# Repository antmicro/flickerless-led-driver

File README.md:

# OSRAM LZ1 LuxiGen LED driver

Copyright (c) 2023 [Antmicro](https://www.antmicro.com) 

## Overview 

This project contains open hardware design files for a PCB supporting a pair of LEDs in LZ1 LuxiGen package from OSRAM.
The PCB includes a flickerless LED driver allowing to adjust LED brightness with a potentiometer.
This design can be easily adopted to other LEDs and eventually can become a custom LED driver providing precise lighting for machine vision applications.

The design files were prepared in KiCad 6.x.

# Key features 

* LED current driver implemented with MPS/MP2483DQ-LF-P
* Designed for a pair of LZ1-00R802-0000
* Can be daisy-chained with multiple LEDs driven with a single driver

## Project structure

The main directory contains KiCad PCB project files, a LICENSE, and a README.
The remaining files are stored in the following directories:

* `lib` - contains the component libraries
* `img` - contains graphics for this README

## Usage

The project contains one PCB that can be configured as a primary or a secondary. 
It is designed to be powered with 12V DC using a barrel jack. It was tested on the highest britgness settings in a chain of 3 boards with a digital microscope as load on USB-C, the current in a circuit was around 1A. 

**Primary board** 

It's the board that contains the LED driver, all the connectors and a potentiometer. 

There are 3 connectors on the primary board: 
* USB-C - outputs 5V without data transfer, only to power some additional device, i.e. a microscope or a camera
* A barrel jack to power the whole circuit wih 12V
* A 2-pin JST connector - to daisy chain boards with diodes in serial connection 

A rotary potentiometer is the element that provides control of diode brightness using the LED driver. 

**Secondary board** 

It only contains the LZ1 diodes, 2-pin connectors and resistors marked as secondary DP (R10 and R7). It is powered and controlled by the primary board through JST connectors. 

> **Single board circuit** 
> To configure the primary board as a standalone, mount the R7 Debug jumper in addition to R11. 

> **Multiboard circuit** 
> To daisy chain the boards R7 CAN NOT be populated on primary board and must be populated on secondary boards. C_out of one board must be connected to A_in of another one. The design was made for 3 boards in a chain. To connect more boards higher voltage and possibly changing some passives will be required. 

## Licensing

This project is published under the [Apache-2.0](LICENSE) license.

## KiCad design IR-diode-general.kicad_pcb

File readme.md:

## Power IR-LEDs driver 
The project consists of 3 similar PCBs. Each of them has 2 LZ1-00R802 diodes. One also has a buck converter that serves as a LED driver for all 3 PCBs. They are daisy-chained into one circuit in order to attach them to a digital microscope, using which we can see through sillicon and observe chip structures.

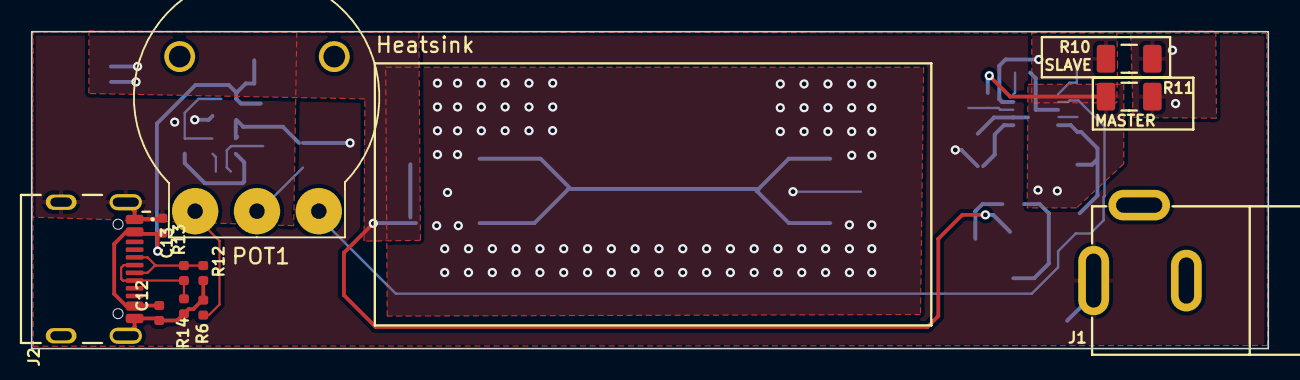
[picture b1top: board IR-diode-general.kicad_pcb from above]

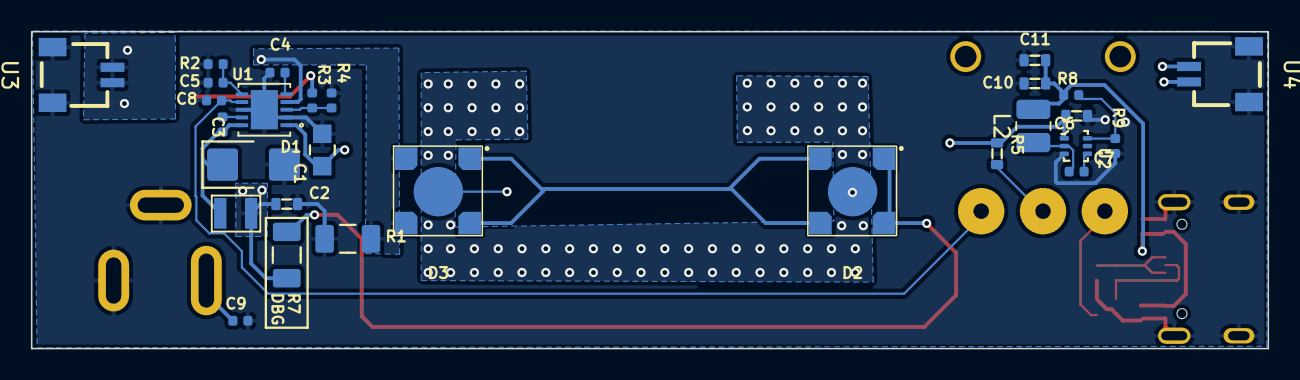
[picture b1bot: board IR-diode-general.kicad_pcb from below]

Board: 2 copper layers, 80.0 x 20.5 mm, 39 parts (28 on the bottom side), 22 nets.

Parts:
C1: C_10u_0805; 0805-cap
C2: C_2u2_0603; 0603-cap
C3, C7, C8, C9, C12, C13: C_100n_0402; C_0402_1005Metric
C4, C5: C_1n0_0402; 0402-cap
C6: C_10u_25V_0603; C_0603_1608Metric
C10, C11: C_22u_0603; C_0603_1608Metric
D1: B360A-M3; DO-214AC
D2, D3: LZ1-00R802-0000; LZ1-00R802_4EP_4.4x4.4
J1: BarrelJack_3167288; BarrelJack_3167288_Horizontal
J2: USB4105-GF-A; GCT_USB4105-GF-A
L1: SRP2512A-4R7M; SRP2512A-1R0M
L2: TFM252012ALMA3R3MTAA; L_1008_2520Metric
POT1: R0141-2-20k; Potentiometer_SRPassives_R0141-2_Horizontal
R1: R_0R2_1206; 1206-res
R2: R_39k_0402; 0402-res
R3: R_18k_0402; 0402-res
R4: R_2k_0402; R_0402_1005Metric
R5: R_300k_0603; 0603-res
R6: R_20k_0402; R_0402_1005Metric
R7, R10, R11: R_0R_1206; R_1206_3216Metric
R8: R_6k8_0402; 0402-res
R9: R_1k3_0402; R_0402_1005Metric
R12, R14: R_10k_0402; R_0402_1005Metric
R13: R_100R_0402; R_0402_1005Metric
U1: MP2483DQ-LF-P
U2: AP62301Z6-7; SOT-563
U3, U4: SM02B-SRSS-TB-LF-SN; JST_SM02B-SRSS-TB(LF)(SN)

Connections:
+12V: C1.2, C6.2, C9.2, J1.1, R5.2, U1.1 (VDD), U2.1 (VIN)
/LED DRIVER & USB-C Power output/VBUS: C10.2, C11.2, C12.2, C13.2, J2.A4 (VBUS), J2.A9 (VBUS), J2.B4 (VBUS), J2.B9 (VBUS), L2.2, R8.2
A_in: D2.2 (A), D2.3 (A), R7.1, U4.1, U4.2
C_out: R10.1, R11.1, U3.1, U3.2
FB: D3.1 (C), D3.4 (C), R1.2, R10.2, U1.4 (FB)
GND: C1.1, C2.1, C4.1, C5.1, C6.1, C8.1, C9.1, C10.1, C11.1, C12.1, C13.1, D1.A, J1.2, J1.3, J2.A1 (GND), J2.A12 (GND), J2.B1 (GND), J2.B12 (GND), J2.S1 (SHIELD), R1.1, R2.1, R4.2, R6.1, R9.1, R12.1, R14.1, U1.2 (VSS), U1.8 (INGND), U1.EPAD, U2.3 (GND), U3.3 (SHIELD), U3.4 (SHIELD), U4.3 (SHIELD), U4.4 (SHIELD)
unnamed: C3.1, D1.K, L1.1, U1.10 (SW)
unnamed: C3.2, U1.9 (BST)
unnamed: C4.2, U1.5 (COMP)
unnamed: C5.2, R2.2, U1.6 (RSET)
unnamed: C7.1, U2.4 (BST)
unnamed: C7.2, L2.1, U2.2 (SW)
unnamed: C8.2, POT1.3, U1.7 (EN/DIM)
unnamed: D2.1 (C), D2.4 (C), D3.2 (A), D3.3 (A)
unnamed: J2.A6 (D+), J2.B6 (D+), R13.1, R14.2
unnamed: J2.A7 (D-), J2.B7 (D-), R12.2, R13.2
unnamed: POT1.1, R6.2
unnamed: POT1.2, R5.1
unnamed: R3.2, R4.1, U1.3 (OVP)
unnamed: R8.1, R9.2, U2.6 (FB)
SW: C2.2, L1.2, R3.1, R7.2, R11.2
Thermal: D2.5 (T), D3.5 (T)

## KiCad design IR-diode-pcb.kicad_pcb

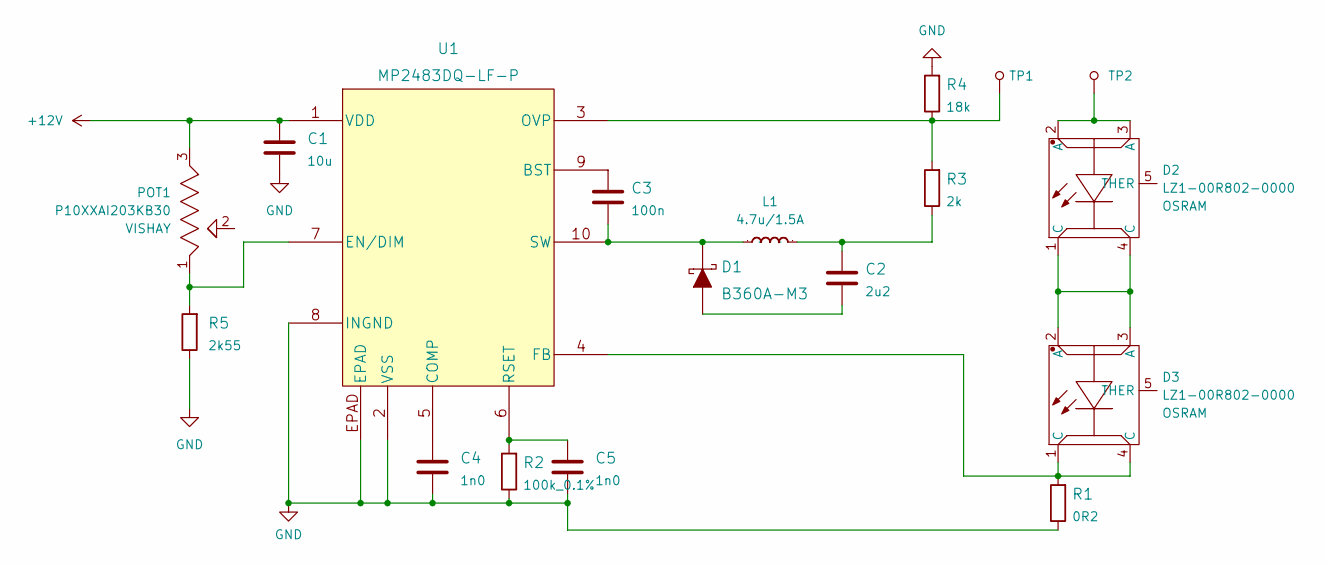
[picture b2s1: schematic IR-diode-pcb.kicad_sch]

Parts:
C1: C_10u_0402; 0402-cap; MPN CC0402MRX5R5BB106
C2: C_2u2_0402; 0402-cap; MPN C1005X5R1A225K050BC
C3: C_100n_0402; 0402-cap; MPN GRM155R61H104KE14D
C4, C5: C_1n0_0402; 0402-cap; MPN 885012005018
D1: B360A-M3; DO-214AC; MPN B360A-M3/61T
D2, D3: LZ1-00R802-0000; LZ1-00R802_4EP_4.4x4.4; MPN LZ1-00R802-0000
L1: SRP2512A-4R7M; SRP2512A-1R0M; MPN SRP2512A-1R0M
POT1: P10XXAI203KB30; MPN P10XXAI203KB30
R1: R_0R2_1206; 1206-res; MPN ERJ-8BSFR20V
R2: R_100k_0.1%_0402; 0402-res; MPN RC0402BR-07100KL
R3: R_2k_0402; 0402-res; MPN CRCW04022K00FKED
R4: R_18k_0402; 0402-res; MPN MCWR04X1802FTL
R5: R_2k55_0402; 0402-res; MPN ERJ-2RKF2551X
TP1, TP2: 5017; PC_TEST-POINT_MINI_3.43x1.78mm; MPN 5017
U1: MP2483DQ-LF-P; MPN MP2483DQ-LF-P

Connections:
+12V: C1.1, POT1.3, U1.1 (VDD)
GND: C1.2, C4.2, C5.2, R1.1, R2.1, R4.2, R5.1, U1.2 (VSS), U1.8 (INGND), U1.EPAD
unnamed: C2.1, L1.2, R3.1
unnamed: C2.2, D1.A
unnamed: C3.1, U1.9 (BST)
unnamed: C3.2, D1.K, L1.1, U1.10 (SW)
unnamed: C4.1, U1.5 (COMP)
unnamed: C5.1, R2.2, U1.6 (RSET)
unnamed: D2.1 (C), D2.4 (C), D3.2 (A), D3.3 (A)
unnamed: POT1.1, R5.2, U1.7 (EN/DIM)
unnamed: D3.1 (C), D3.4 (C), R1.2, U1.4 (FB)
unnamed: R3.2, R4.1, TP1.1, U1.3 (OVP)
unnamed: D2.2 (A), D2.3 (A), TP2.1

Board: 2 copper layers, 18 parts (13 on the bottom side), 13 nets, no tracks yet.

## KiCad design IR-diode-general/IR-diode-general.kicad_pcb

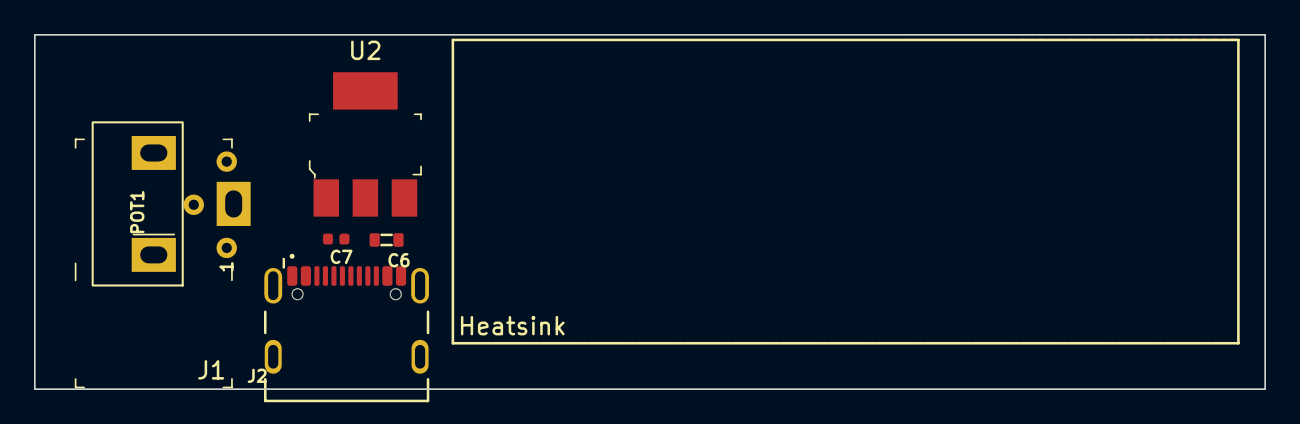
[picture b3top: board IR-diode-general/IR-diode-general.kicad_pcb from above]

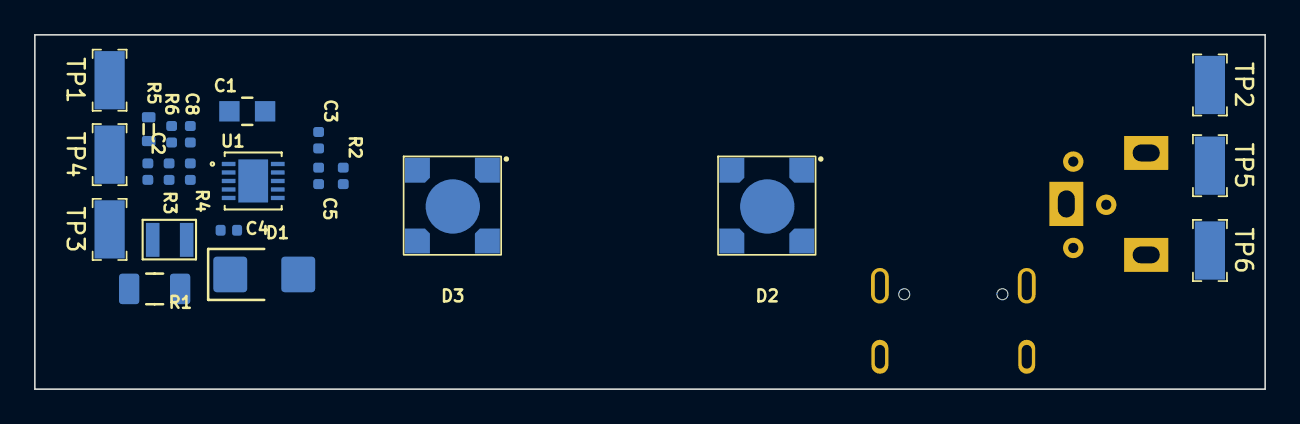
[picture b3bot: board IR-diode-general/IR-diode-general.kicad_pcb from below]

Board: 2 copper layers, 72.4 x 20.9 mm, 29 parts (23 on the bottom side), 15 nets, no tracks yet.

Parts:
C1: C_10u_0805; 0805-cap
C2: C_2u2_0402; C_0402_1005Metric
C3, C8: C_100n_0402; C_0402_1005Metric
C4, C5: C_1n0_0402; 0402-cap
C6: C_10u_16V_0603; 0603-cap
C7: C_22u_0402; C_0402_1005Metric
D1: B360A-M3; DO-214AC
D2, D3: LZ1-00R802-0000; LZ1-00R802_4EP_4.4x4.4
J1: PJ-102A; Barrel_Jack_5.5mmODx2.1mmID_PJ-102A
J2: USB4105-GF-A; GCT_USB4105-GF-A
L1: SRP2512A-4R7M; SRP2512A-1R0M
POT1: P10XXAI203KB30; P10XHAI203KB30
R1: R_0R2_1206; 1206-res
R2: R_100k_0.1%_0402; 0402-res
R3: R_18k_0402; 0402-res
R4: R_2k_0402; R_0402_1005Metric
R5: R_300k_0603; 0603-res
R6: R_20k_0.1%_0402; 0402-res
TP1, TP2, TP3, TP4, TP5, TP6: 5017; PC_TEST-POINT_MINI_3.43x1.78mm
U1: MP2483DQ-LF-P
U2: AZ1117CH-5.0TRG1; SOT-223

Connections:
+12V: C1.2, C6.2, J1.1, R5.2, TP3.1, TP6.1, U1.1 (VDD), U2.3 (VIN)
GND: C1.1, C4.1, C5.1, C6.1, C7.1, C8.1, J1.2, J1.3, J2.A1 (GND), J2.A12 (GND), J2.B1 (GND), J2.B12 (GND), J2.S1 (SHIELD), R1.1, R2.1, R4.2, R6.1, TP4.1, TP5.1, U1.2 (VSS), U1.8 (INGND), U1.EPAD, U2.1 (ADJ/GND)
unnamed: C2.2, L1.2, R3.1, TP1.1
unnamed: C3.1, L1.1, U1.10 (SW)
unnamed: C3.2, U1.9 (BST)
unnamed: C4.2, U1.5 (COMP)
unnamed: C5.2, R2.2, U1.6 (RSET)
unnamed: C7.2, J2.A4 (VBUS), J2.A9 (VBUS), J2.B4 (VBUS), J2.B9 (VBUS), U2.4 (VOUT)
unnamed: D2.1 (C), D2.4 (C), D3.2 (A), D3.3 (A)
unnamed: D2.2 (A), D2.3 (A), TP2.1
unnamed: D3.1 (C), D3.4 (C), R1.2, U1.4 (FB)
unnamed: C8.2, POT1.1, R6.2
unnamed: POT1.2, U1.7 (EN/DIM)
unnamed: POT1.3, R5.1
unnamed: R3.2, R4.1, U1.3 (OVP)

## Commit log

2023-03-30 MP2483DQ-LF-P converter
2023-11-07 Power rail routing changes
2023-11-07 Updated design rules
2023-11-07 README: small fix
2023-11-07 Add preliminary layout
2023-11-07 Correct symbols and footprints with missing 3D models
2023-11-07 Refresh standardization on schematic and PCB
2023-11-07 Layout tweaks
2023-11-07 Update naming convention
2023-11-07 [50954] Added CC resistors and OHP assets, updated README
2023-11-07 Change diodes power rail labels
2023-11-07 Changed the 12V-5V converter
2023-11-07 Introduced hierarchical schematics
2023-11-07 Rearranged project structure
2023-11-07 Correct sch logos. Update PCB from schematic
2023-11-07 Bump revision to 1.1. Update the PCB signage
2023-11-07 Added USB-C and power barrel connector
2023-11-07 Improving power rail tracks and planes
2023-11-07 Added notes on U1 configuration
2023-11-07 Configured page properties
2023-11-07 Refactor README
2023-11-07 Converter configured, pcb started
2023-11-07 Cleanup
2023-11-07 Layout and schematic updates
2023-11-07 README update
2023-11-07 Add thermal pad label
2023-11-07 Added pull down resistors on USB
2023-11-07 Updated Value fields in selected footprints
2023-11-07 B2B connectors symbol adjusted
2023-11-07 Changed the potentiometer to R0141-2-20k
2023-11-07 Introduced schematic standardization
2023-11-07 Add BOM
2023-11-07 Refresh PCB
2023-11-07 Add 100n to VBUS, schematic cleanup
2023-11-07 Added signage
2023-11-07 Cleanup - remove generated files
2023-11-07 README updates, board naming unification
2023-11-07 Add LICENSE
2023-11-07 Change pinout of B2B connectors
2023-11-07 Changed R2
2023-11-07 Added OSHW marking
2023-11-07 Finalized board layout

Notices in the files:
parts and their libraries:
Copyright: Copyright (c) 2023 Antmicro
License: Apache-2.0 License
License: Apache-2.0
